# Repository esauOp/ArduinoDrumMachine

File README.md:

ArduinoDrumMachine
==================

Diseños esquemáticos para la elaboración casera de una BleepDrum

* All work licensed under a Creative Commons Attribution-ShareAlike 3.0 Unported License

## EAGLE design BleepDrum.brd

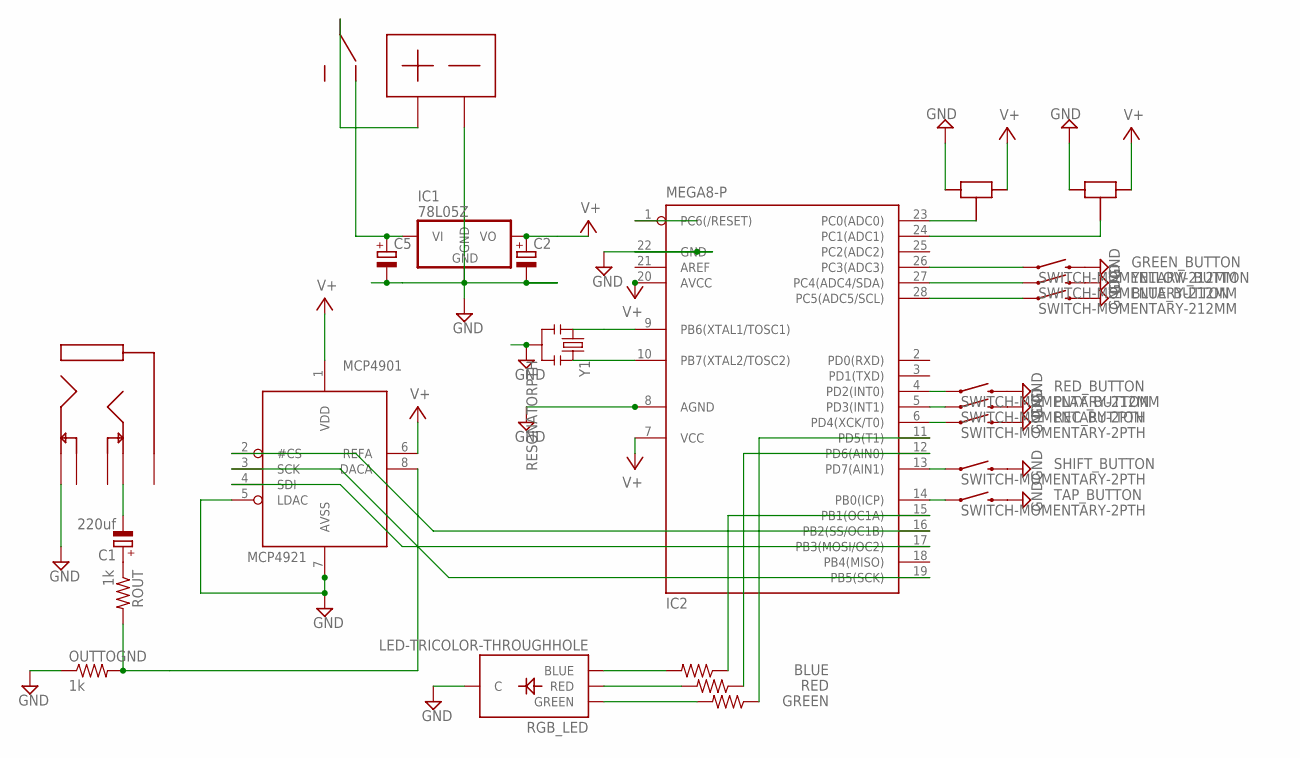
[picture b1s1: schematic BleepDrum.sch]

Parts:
BLUE: RESISTORPTH-1/6W; 1/6W-RES
BLUE_BUTTON: SWITCH-MOMENTARY-212MM; TACTILE-PTH-12MM
C1: 220uf; E2,5-6
C2, C5: CPOL-EUE2.5-6; E2,5-6
GREEN: RESISTORPTH-1/6W; 1/6W-RES
GREEN_BUTTON: SWITCH-MOMENTARY-212MM; TACTILE-PTH-12MM
IC1: 78L05Z; TO92
IC2: MEGA8-P; DIL28-3
LEFT_POT: POT
MCP4901: MCP4921; DIL08
OUTTOGND: 1k; 1/6W-RES
PLAY_BUTTON: SWITCH-MOMENTARY-2PTH; TACTILE-PTH
REC_BUTTON: SWITCH-MOMENTARY-2PTH; TACTILE-PTH
RED: RESISTORPTH-1/6W; 1/6W-RES
RED_BUTTON: SWITCH-MOMENTARY-212MM; TACTILE-PTH-12MM
RGB_LED: LED-TRICOLOR-THROUGHHOLE
RIGHT_POT: POT
ROUT: 1k; 1/6W-RES
SHIFT_BUTTON: SWITCH-MOMENTARY-2PTH; TACTILE-PTH
SW1: SLIDE_HORIZ_OS
TAP_BUTTON: SWITCH-MOMENTARY-2PTH; TACTILE-PTH
U$7: 9VSMALPINS; 9VSMALLPINS
U$8: 1/8STEREO
Y1: RESONATORPTH; RESONATOR-PTH
YELLOW_BUTTON: SWITCH-MOMENTARY-212MM; TACTILE-PTH-12MM

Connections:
GND: BLUE_BUTTON.3 (2), C2.-, C5.-, GREEN_BUTTON.3 (2), IC1.2 (GND), IC2.8 (AGND), IC2.22 (GND), LEFT_POT.P$3, MCP4901.5 (LDAC), MCP4901.7 (AVSS), OUTTOGND.1, PLAY_BUTTON.3 (2), REC_BUTTON.3 (2), RED_BUTTON.3 (2), RGB_LED.GND (C), RIGHT_POT.P$3, SHIFT_BUTTON.3 (2), TAP_BUTTON.3 (2), U$7.P$2, U$8.P$2, Y1.2, YELLOW_BUTTON.3 (2)
unnamed: IC2.10 (PB7(XTAL2/TOSC2)), Y1.3
unnamed: BLUE.1, IC2.15 (PB1(OC1A))
unnamed: IC2.12 (PD6(AIN0)), RED.1
unnamed: GREEN.1, IC2.11 (PD5(T1))
unnamed: IC2.9 (PB6(XTAL1/TOSC1)), Y1.1
unnamed: IC2.17 (PB3(MOSI/OC2)), MCP4901.4 (SDI)
unnamed: SW1.P$1, U$7.P$1
unnamed: IC2.19 (PB5(SCK)), MCP4901.3 (SCK)
unnamed: IC2.23 (PC0(ADC0)), RIGHT_POT.P$2
unnamed: IC2.24 (PC1(ADC1)), LEFT_POT.P$2
unnamed: C1.+, ROUT.1
unnamed: MCP4901.8 (DACA), OUTTOGND.2, ROUT.2
unnamed: BLUE.2, RGB_LED.GRN (BLUE)
unnamed: RED.2, RGB_LED.BLU (RED)
unnamed: GREEN.2, RGB_LED.RED (GREEN)
unnamed: IC2.5 (PD3(INT1)), PLAY_BUTTON.1
unnamed: C1.-, U$8.P$5
unnamed: IC2.27 (PC4(ADC4/SDA)), YELLOW_BUTTON.1
unnamed: C5.+, IC1.3 (VI), SW1.P$2
unnamed: C2.+, IC1.1 (VO), IC2.7 (VCC), IC2.20 (AVCC), LEFT_POT.P$1, MCP4901.1 (VDD), MCP4901.6 (REFA), RIGHT_POT.P$1
unnamed: IC2.14 (PB0(ICP)), TAP_BUTTON.1
unnamed: IC2.6 (PD4(XCK/T0)), REC_BUTTON.1
unnamed: IC2.13 (PD7(AIN1)), SHIFT_BUTTON.1
unnamed: GREEN_BUTTON.1, IC2.26 (PC3(ADC3))
unnamed: BLUE_BUTTON.1, IC2.28 (PC5(ADC5/SCL))
unnamed: IC2.16 (PB2(SS/OC1B)), MCP4901.2 (#CS)
P1: IC2.4 (PD2(INT0)), RED_BUTTON.1

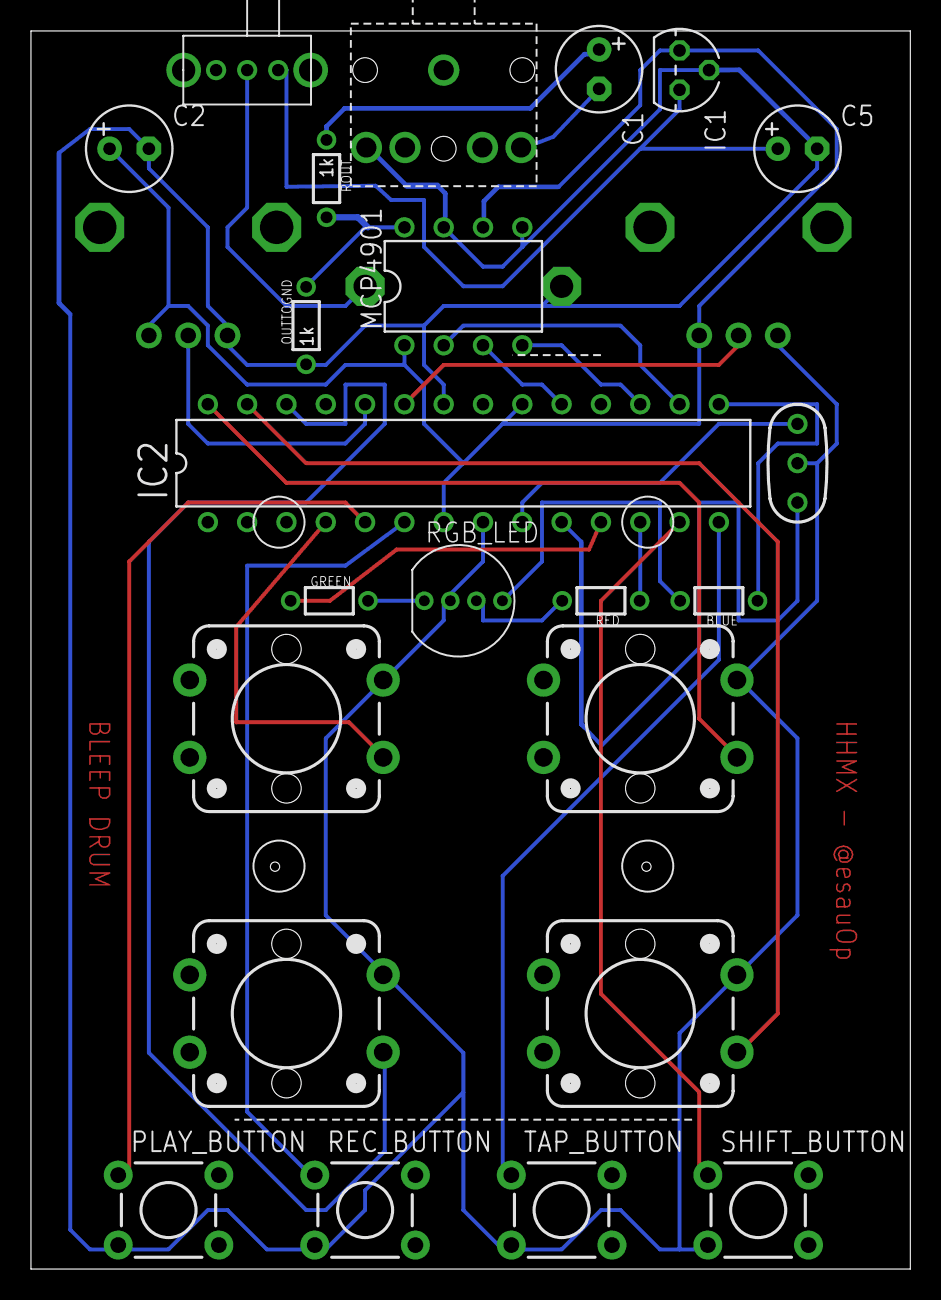
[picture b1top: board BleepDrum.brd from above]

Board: 2 copper layers, 56.8 x 80.0 mm, 26 parts (0 on the bottom side), 28 nets.

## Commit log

2014-04-13 Adding schematics...
2014-04-13 License added
2014-04-13 Adding PDFs...

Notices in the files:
parts and their libraries:
SparkFun-Passives: Licensing: CC v3.0 Share-Alike You are welcome to use this library for commercial purposes.
